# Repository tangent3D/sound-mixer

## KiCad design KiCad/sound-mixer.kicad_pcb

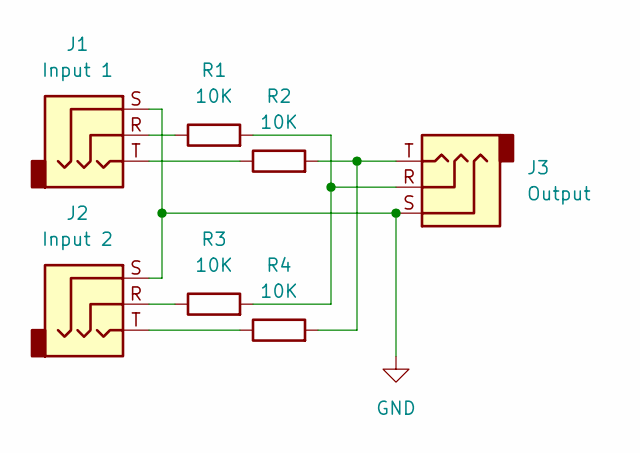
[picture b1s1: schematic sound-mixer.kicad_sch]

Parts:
J1: Input 1; Jack_3.5mm_CUI_SJ1-3523N_Horizontal
J2: Input 2; Jack_3.5mm_CUI_SJ1-3523N_Horizontal
J3: Output; Jack_3.5mm_CUI_SJ1-3523N_Horizontal
R1, R2, R3, R4: 10K; R_Axial_DIN0207_L6.3mm_D2.5mm_P7.62mm_Horizontal

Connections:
GND: J1.S, J2.S, J3.S
unnamed: J1.R, R1.1
unnamed: J1.T, R2.1
unnamed: J3.R, R1.2, R3.2
unnamed: J3.T, R2.2, R4.2
unnamed: J2.R, R3.1
unnamed: J2.T, R4.1

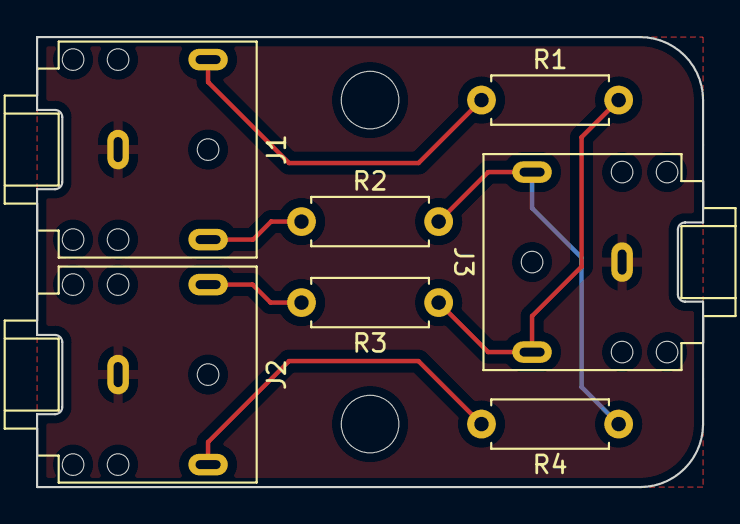
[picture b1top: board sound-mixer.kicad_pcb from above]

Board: 2 copper layers, 37.0 x 25.0 mm, 7 parts (0 on the bottom side), 7 nets.
